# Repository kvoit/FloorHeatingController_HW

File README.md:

# Floor heating hardware

Contoller board for up to 10 floor heading circuits. Thermostats via MQTT or 868MHz RF (to be developed).
Changed from 1-Wire to 868MHz connectivity in version 2.0.

## Controller

Central controller for my floor heating based on the ESP32.

### Connectivity

- Wifi (MQTT implemented) and BTLE (currently unused) from ESP32.
- AES encrypted and optionaly ATSHA204 authenticated 868MHz radio (to be implemented).
- 10 low-side switched outputs that can be individually controlled and output the input voltage. (Speed limited by the shift registers. Hardware SPI theoretically possible but untested.) Used to power valves.
- 4 Qwiic-compatible I2C ports
- 1 ~7.5V/5V/3.3V/GND ports for powering thermostats.
- JTAG header

### Case

Can be mounted in small breaker boxes on DIN rails. Display fits into the opening for breakers.

### Images

### Software

Software [here](https://github.com/kvoit/FloorHeatingController_HW)

## Thermostat

Coming soon ...

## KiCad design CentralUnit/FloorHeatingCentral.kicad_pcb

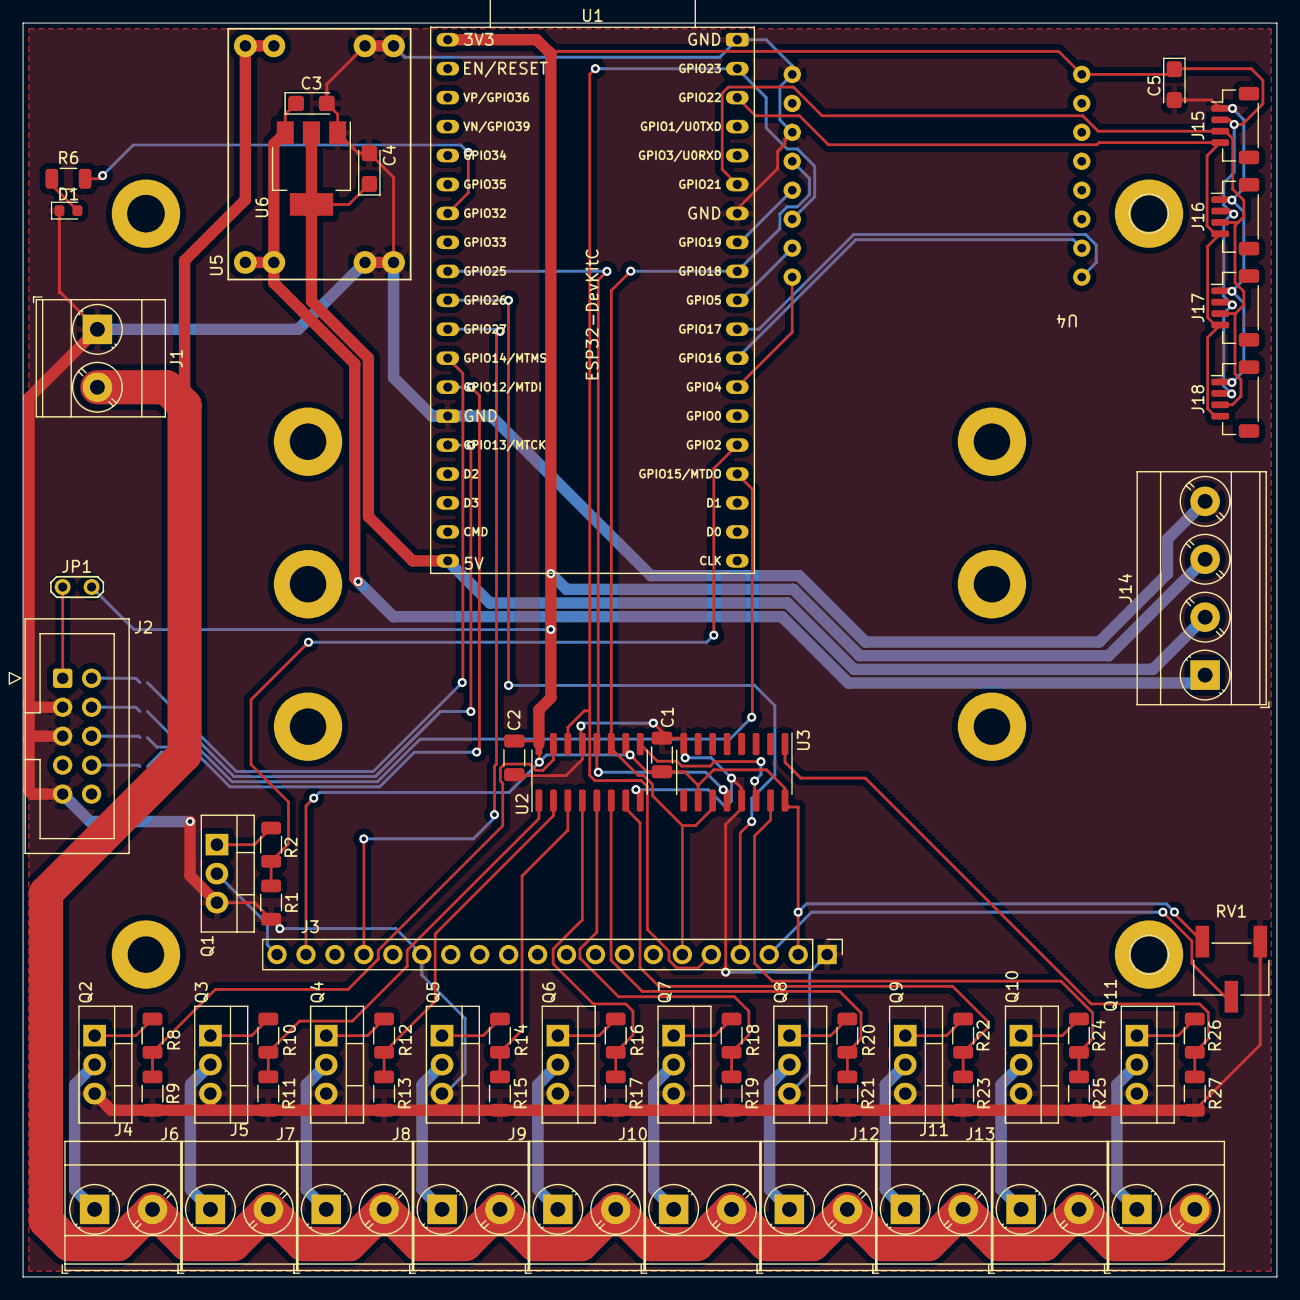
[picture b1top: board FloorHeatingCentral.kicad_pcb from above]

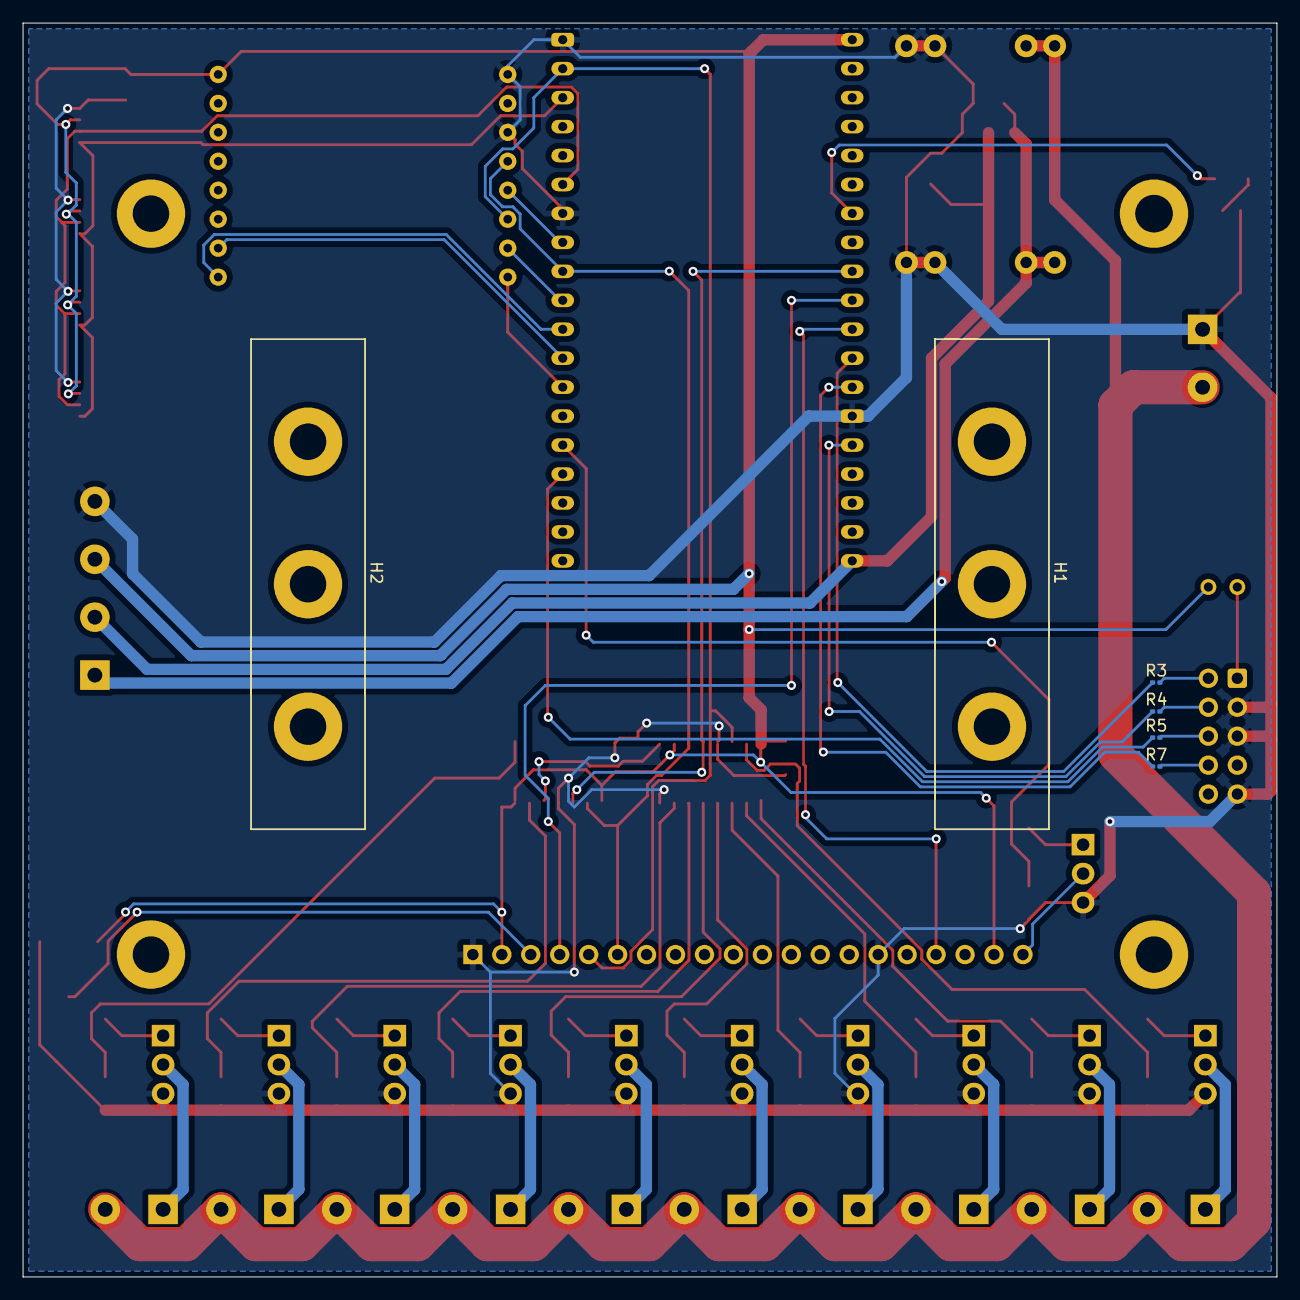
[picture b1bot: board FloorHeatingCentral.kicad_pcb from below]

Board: 2 copper layers, 110.0 x 110.0 mm, 72 parts (6 on the bottom side), 63 nets.

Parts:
C1, C2: 0.1u; C_1206_3216Metric
C3, C4, C5: 10u; CP_EIA-3216-18_Kemet-A
D1: LED; LED_0603_1608Metric
H1, H2: MountingHole; PCB_DINrail_holder
J1, J4, J5, J6, J7, J8, J9, J10, J11, J12, J13: Screw_Terminal_01x02; TerminalBlock_Phoenix_MKDS-3-2-5.08_1x02_P5.08mm_Horizontal
J2: Conn_02x05_Odd_Even; IDC-Header_2x05_P2.54mm_Vertical
J3: Conn_01x20; 12864_LCD_128x64
J14: Screw_Terminal_01x04; TerminalBlock_Phoenix_MKDS-3-4-5.08_1x04_P5.08mm_Horizontal
J15, J16, J17, J18: Conn_01x04_Male; JST_SH_BM04B-SRSS-TB_1x04-1MP_P1.00mm_Vertical
JP1: Jumper_2_Open; TestPoint_2Pads_Pitch2.54mm_Drill0.8mm
Q1, Q2, Q3, Q4, Q5, Q6, Q7, Q8, Q9, Q10, Q11: Q_NMOS_GDS; TO-220-3_Vertical
R1, R9, R11, R13, R15, R17, R19, R21, R23, R25, R27: 10K; R_1206_3216Metric
R2, R8, R10, R12, R14, R16, R18, R20, R22, R24, R26: 560R; R_1206_3216Metric
R3, R4, R5, R7: 100R; R_0201_0603Metric
R6: 660R; R_1206_3216Metric
RV1: R_POT; Potentiometer_Bourns_3269W_Vertical
U1: ESP32-DevKitC
U2, U3: 74HC595D_118; SOIC-16_3.9x9.9mm_P1.27mm
U4: RFM69-ATSHA-breakout; RFM69HCW_ATSHA204A_Breakout
U5: MP1584
U6: LM1117-5.0; SOT-223-3_TabPin2

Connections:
+3V3: C1.2, C2.2, C5.1, J3.2, J3.19, J14.3, J15.2, J16.2, J17.2, J18.2, JP1.1 (A), RV1.3, U1.1 (3V3), U2.10 (~SRCLR), U2.16 (VCC), U3.10 (~SRCLR), U3.16 (VCC), U4.8 (+3V3)
+5V: C4.1, J14.2, U1.19 (5V), U6.2 (VO)
+7.5V: C3.1, J14.1, U5.3 (VOUT), U6.3 (VI)
+24V: J1.2, J4.2, J5.2, J6.2, J7.2, J8.2, J9.2, J10.2, J11.2, J12.2, J13.2, U5.1 (VIN)
/ATSHA: U1.26 (ADC2_CH0/GPIO4), U4.16 (ATSHA)
/ActuatorConn/GATE: R8.1, R9.1, U2.15 (QA)
/ActuatorConn/ValSW: J4.1, Q2.2 (D)
/DISP_CS: J3.4, U1.10 (DAC_2/ADC2_CH9/GPIO26)
/DISP_RST: J3.17, U1.11 (ADC2_CH7/GPIO27)
/DL_SW: R1.1, R2.1, U1.24 (ADC2_CH2/*GPIO2)
/GND_DL_SW: J3.20, Q1.2 (D)
/LED: R6.2, U1.7 (32K_XP/GPIO32/ADC1_CH4)
/RFM69_CS: U1.29 (*GPIO5), U4.15 (NSS)
/RFM69_IRQ: U1.27 (GPIO16), U4.2 (DIO0)
/RFM69_RST: U1.28 (GPIO17), U4.1 (RST)
/SCL: J15.4, J16.4, J17.4, J18.4, U1.36 (GPIO22)
/SDA: J15.3, J16.3, J17.3, J18.3, U1.33 (GPIO21)
/SR_LATCH: U1.9 (DAC_1/ADC2_CH8/GPIO25), U2.12 (RCLK), U3.12 (RCLK)
/TCK: R4.1, U1.15 (MTCK/GPIO13/ADC2_CH4)
/TDI: R7.1, U1.13 (*MTDI/GPIO12/ADC2_CH5)
/TDO: R5.1, U1.23 (*MTDO/GPIO15/ADC2_CH3)
/TMS: R3.1, U1.12 (MTMS/GPIO14/ADC2_CH6)
/VSPI_MISO: U1.31 (GPIO19), U4.13 (MISO)
/VSPI_MOSI: J3.5, U1.37 (GPIO23), U2.14 (SER), U4.14 (MOSI)
/VSPI_SCK: J3.6, U1.30 (GPIO18), U2.11 (SRCLK), U3.11 (SRCLK), U4.12 (SCK)
/sheet5C0162C8/GATE: R10.1, R11.1, U2.1 (QB)
/sheet5C0162C8/ValSW: J5.1, Q3.2 (D)
/sheet5C0163D9/GATE: R12.1, R13.1, U2.2 (QC)
/sheet5C0163D9/ValSW: J6.1, Q4.2 (D)
/sheet5C0163DC/GATE: R14.1, R15.1, U2.3 (QD)
/sheet5C0163DC/ValSW: J7.1, Q5.2 (D)
/sheet5C0169FB/GATE: R24.1, R25.1, U3.15 (QA)
/sheet5C0169FB/ValSW: J12.1, Q10.2 (D)
/sheet5C0169FE/GATE: R26.1, R27.1, U3.1 (QB)
/sheet5C0169FE/ValSW: J13.1, Q11.2 (D)
/sheet5C01653A/GATE: R18.1, R19.1, U2.5 (QF)
/sheet5C01653A/ValSW: J9.1, Q7.2 (D)
/sheet5C01653D/GATE: R20.1, R21.1, U2.6 (QG)
/sheet5C01653D/ValSW: J10.1, Q8.2 (D)
/sheet5C016537/GATE: R16.1, R17.1, U2.4 (QE)
/sheet5C016537/ValSW: J8.1, Q6.2 (D)
/sheet5C016540/GATE: R22.1, R23.1, U2.7 (QH)
/sheet5C016540/ValSW: J11.1, Q9.2 (D)
GND: C1.1, C2.1, C3.2, C4.2, C5.2, D1.1 (K), J1.1, J2.3, J2.5, J2.9, J3.1, J3.15, J14.4, J15.1, J16.1, J17.1, J18.1, Q1.3 (S), Q2.3 (S), Q3.3 (S), Q4.3 (S), Q5.3 (S), Q6.3 (S), Q7.3 (S), Q8.3 (S), Q9.3 (S), Q10.3 (S), Q11.3 (S), R1.2, R9.2, R11.2, R13.2, R15.2, R17.2, R19.2, R21.2, R23.2, R25.2, R27.2, RV1.1, U1.14 (GND), U1.32 (GND), U1.38 (GND), U2.8 (GND), U2.13 (~OE), U3.8 (GND), U3.13 (~OE), U4.9 (GND), U4.11 (GND), U5.2 (GND_IN), U5.4 (GND_OUT), U6.1 (GND)
unnamed: D1.2 (A), R6.1
unnamed: J2.1, JP1.2 (B)
unnamed: J2.2, R3.2
unnamed: J2.4, R4.2
unnamed: J2.6, R5.2
unnamed: J2.8, R7.2
unnamed: J3.3, RV1.2
unnamed: Q1.1 (G), R2.2
unnamed: Q2.1 (G), R8.2
unnamed: Q3.1 (G), R10.2
unnamed: Q4.1 (G), R12.2
unnamed: Q5.1 (G), R14.2
unnamed: Q6.1 (G), R16.2
unnamed: Q7.1 (G), R18.2
unnamed: Q8.1 (G), R20.2
unnamed: Q9.1 (G), R22.2
unnamed: Q10.1 (G), R24.2
unnamed: Q11.1 (G), R26.2
unnamed: U2.9 (QH'), U3.14 (SER)

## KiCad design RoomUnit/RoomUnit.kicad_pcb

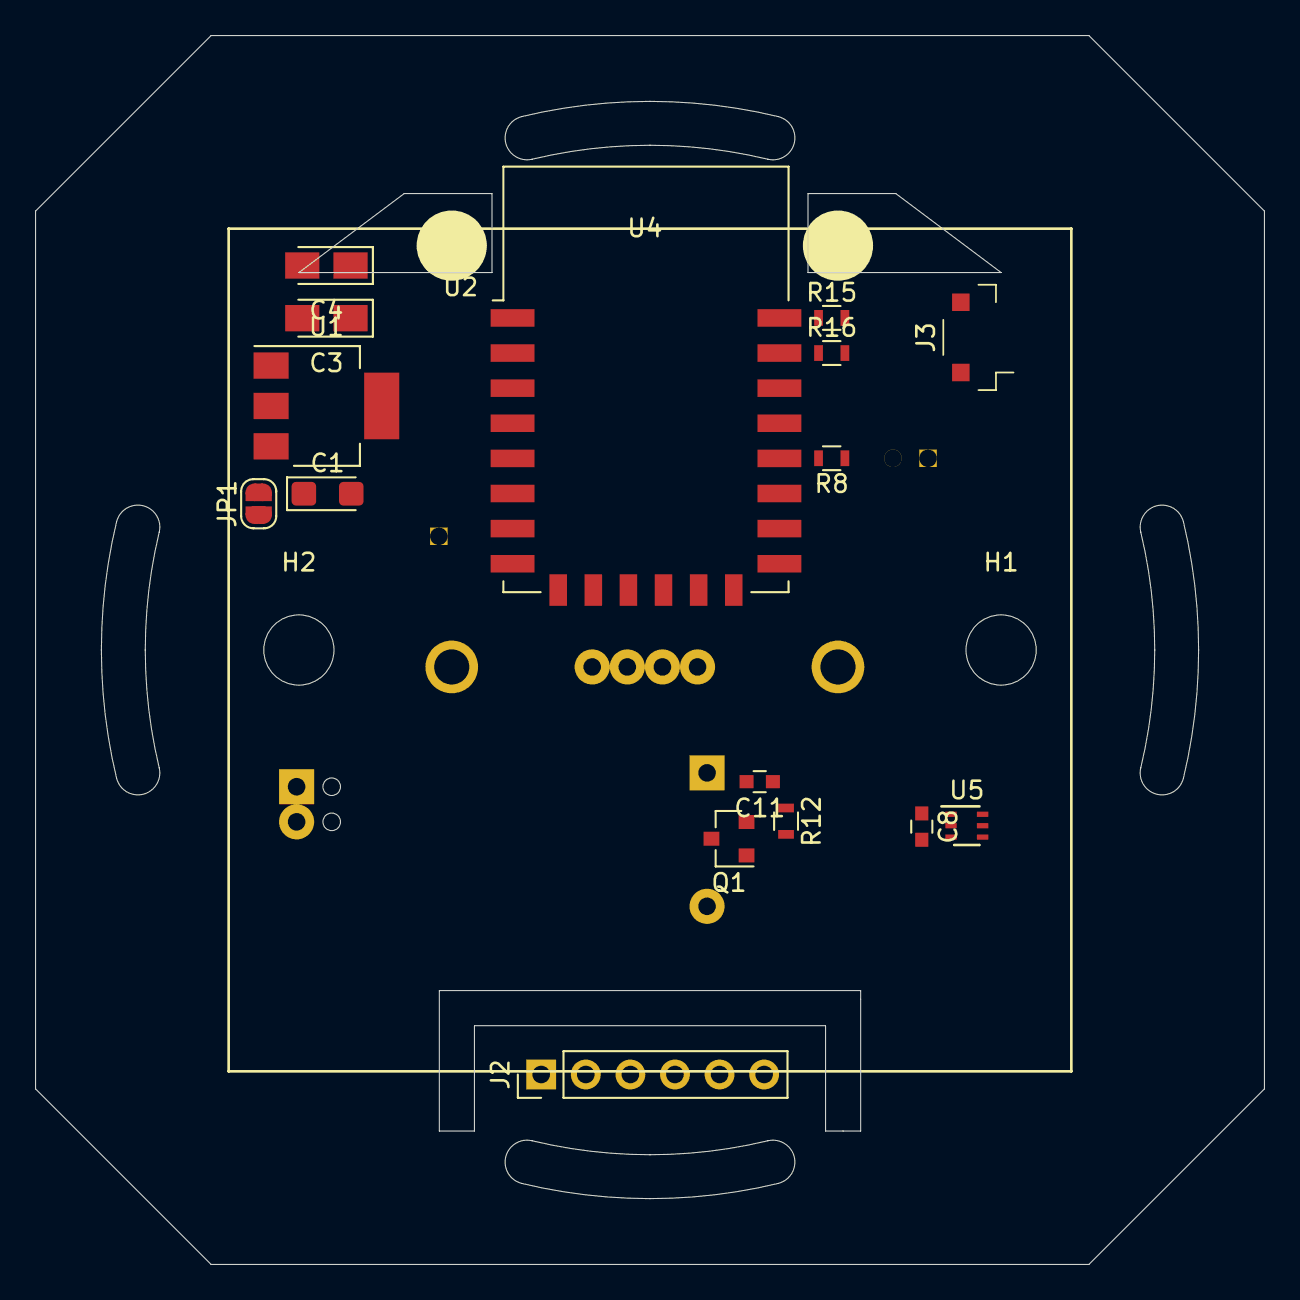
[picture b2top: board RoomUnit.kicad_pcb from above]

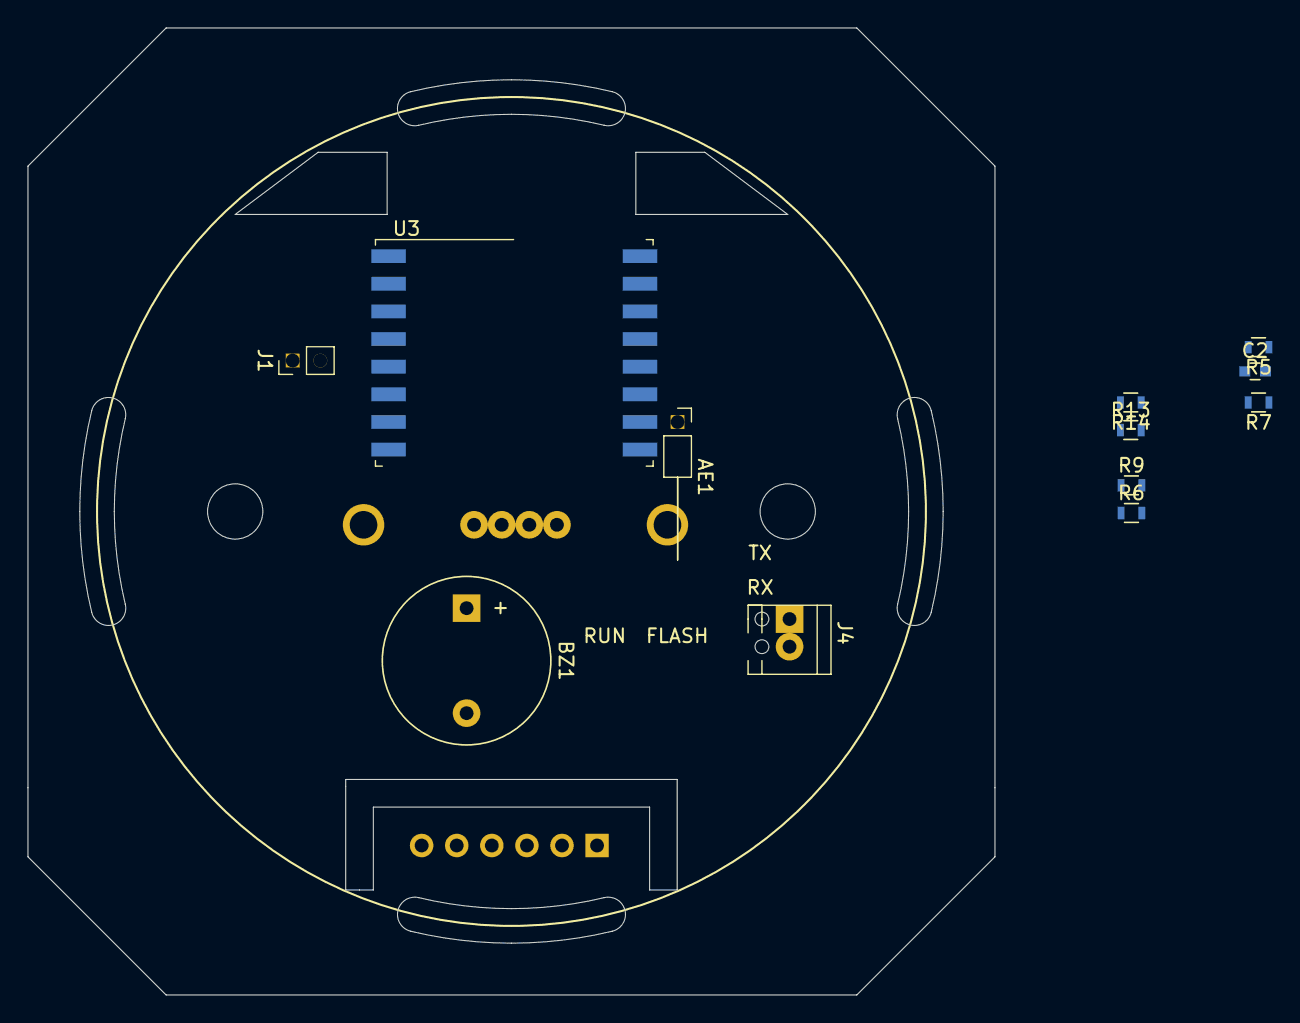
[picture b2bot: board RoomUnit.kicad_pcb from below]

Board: 2 copper layers, 70.0 x 70.0 mm, 31 parts (12 on the bottom side), 20 nets, no tracks yet.

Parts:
AE1: Antenna; PinHeader_1x01_P2.54mm_Horizontal
BZ1: Buzzer; Buzzer_12x9.5RM7.6
C1: 10u; CP_EIA-3216-18_Kemet-A
C2: 100n; C_0603
C3, C4: 10u; CP_Tantalum_Case-A_EIA-3216-18_Reflow
C8: 100u; C_0603
C11: C; C_0603
H1, H2: MountingHole; MountingHole_4mm
J1: Conn_01x02_Male; PinHeader_1x02_P2.54mm_Vertical
J2: Conn_01x06_Female; PinHeader_1x06_P2.54mm_Vertical
J3: Conn_01x04_Male; JST_SH_BM04B-SRSS-TB_1x04-1MP_P1.00mm_Vertical
J4: Screw_Terminal_01x02; TerminalBlock_Phoenix_MPT-0,5-2-2.54_1x02_P2.54mm_Horizontal
JP1: SolderJumper_2_Bridged; SolderJumper-2_P1.3mm_Open_RoundedPad1.0x1.5mm
Q1: BC817; SOT-23
R5, R6, R7, R8, R9, R13, R14: 10k; R_0603
R12: 2k2; R_0603
R15, R16: 470R; R_0603
U1: LM1117-3.3; SOT-223-3_TabPin2
U2: ESP-12F; ESP-12E
U3: RFM69HW; HOPERF_RFM69HW
U4: 1.3"_128x64OLED_I2C; OLED128x64
U5: LTR-303ALS-01; Lite-On_LTR-303ALS-01

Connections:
+3V3: C3.1, C8.1, J2.1, J2.5, J2.6, J3.4, JP1.2 (B), R5.2, R7.2, R9.2, R13.2, R14.1, U1.2 (VO), U2.8 (VCC), U4.2 (VCC), U5.1 (VDD)
+5V: BZ1.1 (-), C1.1, J4.2, JP1.1 (A), U1.3 (VI)
/BUZZ: R12.2, U2.7 (GPIO13)
/CH_PD: R7.1, U2.3 (EN)
/GPIO0: R8.1, U2.18 (GPIO0)
/GPIO2: R9.1, U2.17 (GPIO2)
/GPIO15: R6.1, U2.16 (GPIO15)
/RST: C2.2, R5.1, U2.1 (~RST)
/RxD: R16.1, U2.21 (GPIO3/RXD)
/SCL: J2.3, R14.2, U2.20 (GPIO5), U4.3 (SCL), U5.4 (SCL)
/SDA: J2.4, R13.1, U2.19 (GPIO4), U4.4 (SDA), U5.6 (SDA)
/TxD: R15.1, U2.22 (GPIO1/TXD)
GND: C1.2, C2.1, C4.2, C8.2, C11.2, J1.1, J2.2, J3.1, J4.1, Q1.2 (E), R6.2, U1.1 (GND), U2.15 (GND), U4.1 (GND), U5.3 (GND)
unnamed: AE1.1 (A), U3.10 (ANA)
unnamed: BZ1.2 (+), Q1.3 (C)
unnamed: C11.1, Q1.1 (B), R12.1
unnamed: J3.2, R15.2
unnamed: J3.3, R16.2
unnamed: J1.2, R8.2
unnamed: U3.9 (GND), U3.11 (GND)

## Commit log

2018-11-27 First version of central controller.
2018-11-27 Some improvements
2018-12-02 Added thermostat unit
2019-01-12 V2 with fixed SPI bus, status LED und changed flash header
2019-01-27 Bugfixes: Wrong use of GPIO15, removed header for GPIO2
2019-09-14 Added alternative resistor to connect LCD brightness to DAC
2019-10-23 Added possibility to PWM LCD light and updated README
2022-04-27 Major work changing over to 868MHz solution. Current state unfinished
2022-04-28 CLeanup
2022-04-28 Updated gitignore
2022-04-28 More cleanup and potentially final routing
2022-04-28 Added power port for thermostats
2022-04-28 Minor changes
2022-05-01 Added I2c ports. Final routing. Production.
2022-05-01 Silkscreen improvement
